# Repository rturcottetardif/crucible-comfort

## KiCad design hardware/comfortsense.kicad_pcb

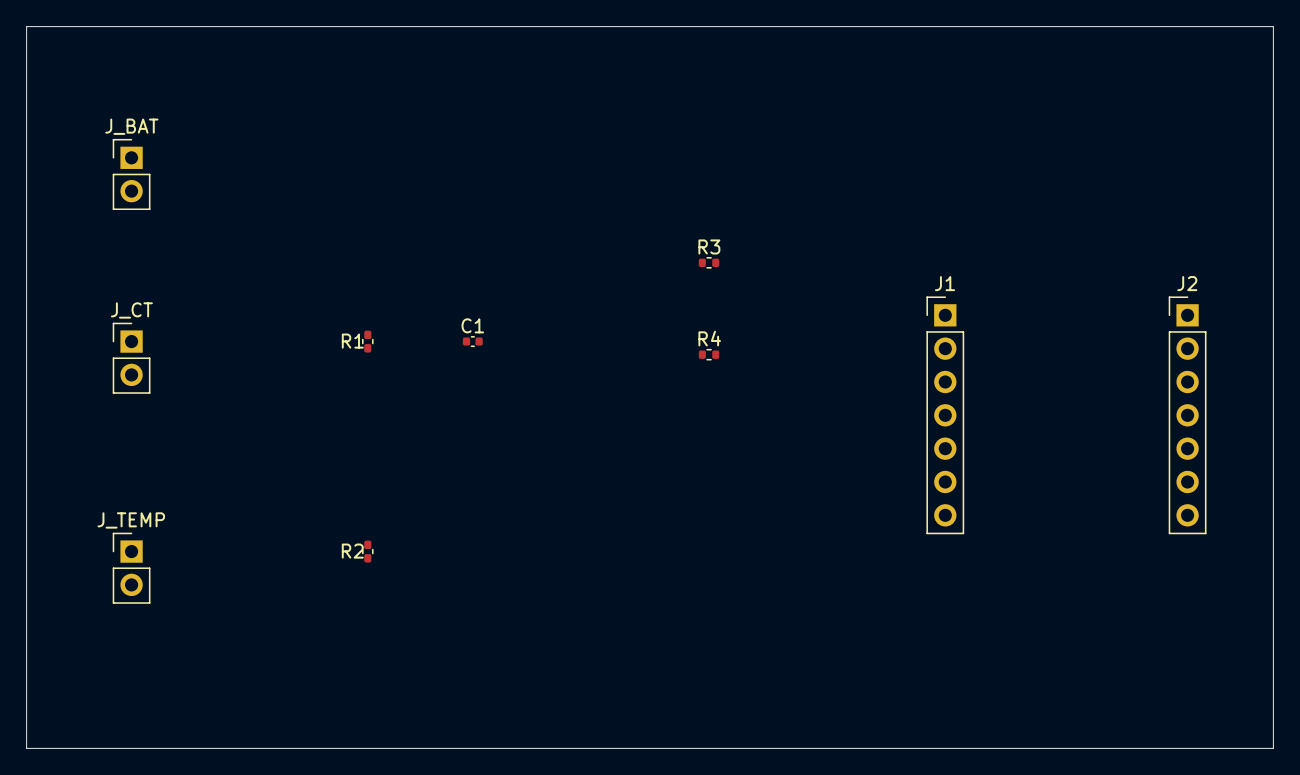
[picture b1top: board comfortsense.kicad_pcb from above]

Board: 2 copper layers, 95.0 x 55.0 mm, 10 parts (0 on the bottom side), 7 nets, no tracks yet.

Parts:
C1: 100nF; C_0402_1005Metric
J1: XIAO-Left; PinHeader_1x07_P2.54mm_Vertical
J2: XIAO-Right; PinHeader_1x07_P2.54mm_Vertical
J_BAT: Battery-2P; PinHeader_1x02_P2.54mm_Vertical
J_CT: CT-Clamp-3.5mm; PinHeader_1x02_P2.54mm_Vertical
J_TEMP: NTC-Probe; PinHeader_1x02_P2.54mm_Vertical
R1: 68R; R_0402_1005Metric
R2, R3, R4: 10k; R_0402_1005Metric

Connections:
+3V3: R2.1, R3.1, R4.1
ADC_CT: C1.1, J1.3, R1.2
ADC_TEMP: J1.4, J_TEMP.1, R2.2
CT_IN_P: J_CT.1, R1.1
GND: C1.2, J1.7, J2.6, J_BAT.2, J_TEMP.2
SCL: J1.6, R4.2
SDA: J1.5, R3.2

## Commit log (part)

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2026-04-14 test
2026-04-14 add .gitignore
2026-04-15 day 1
2026-04-17 after specs step
2026-05-13 transcripts
2026-05-20 chore: close Stage 1 — compact case law, freeze precedents
    8 entries frozen (Cases 2–7, Direct ΔP SOR, First Scaffold SOR, Path B Waiver SOR).
    Stage 1 gate: Path A 8/8 PASS (2026-05-19). Path B waived — RenoneBridge deferred.
    Amendments ratified during Stage 1: A5, A6, A7, A9, A11.
    Bills enacted: 1, 2-A, 2-B, 2-D, 3, 4.
